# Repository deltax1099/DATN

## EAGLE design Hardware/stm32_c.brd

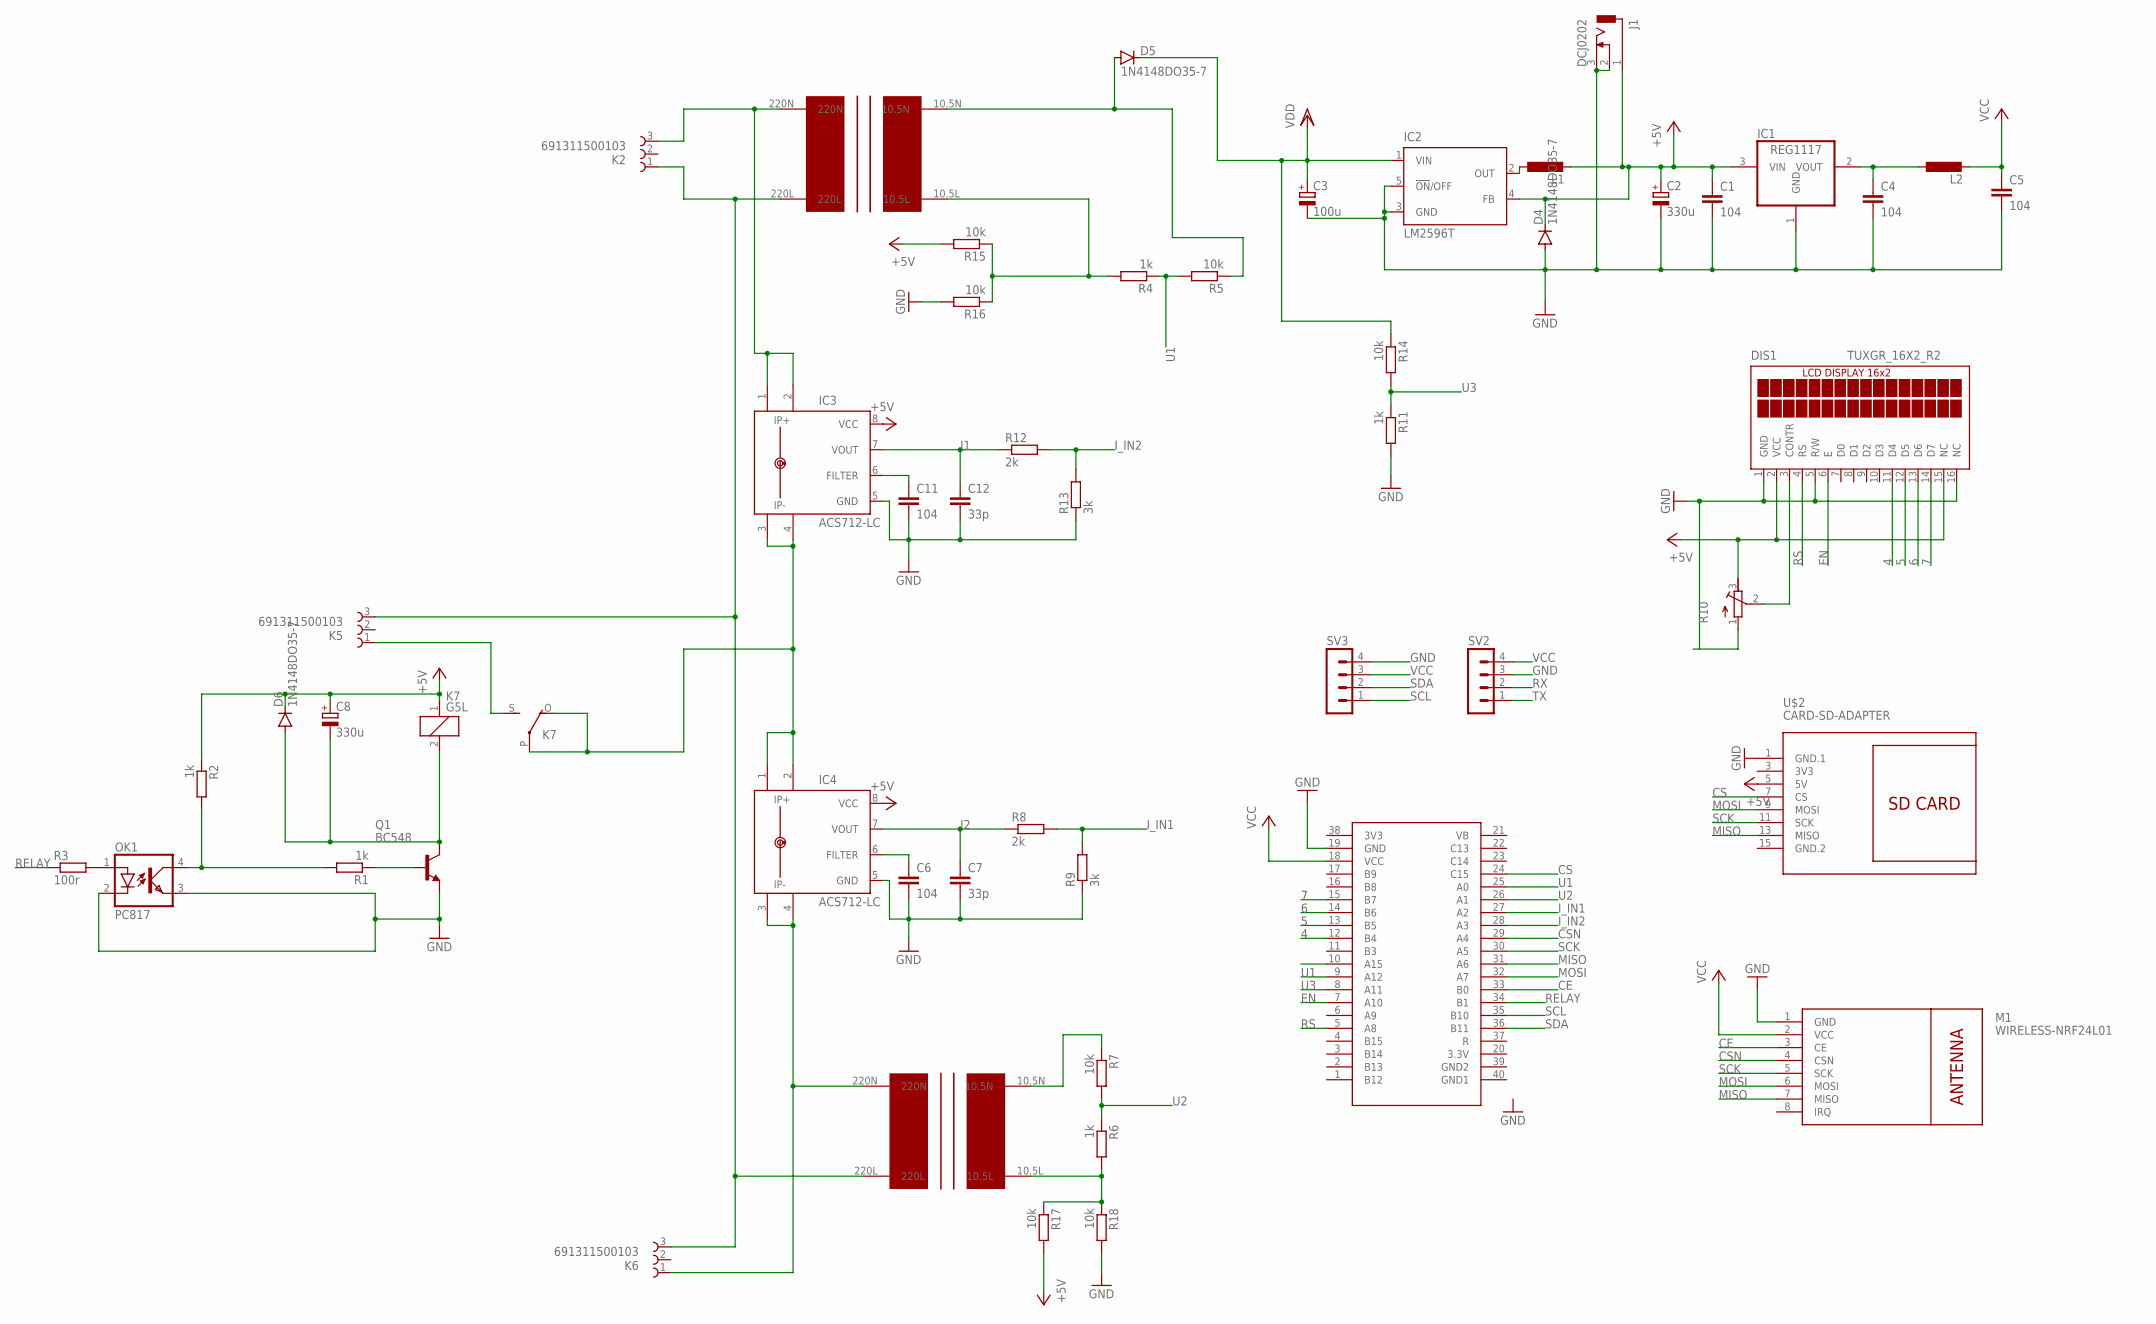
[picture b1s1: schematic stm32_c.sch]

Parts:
C1, C4, C5, C6, C11: 104; C050-025X075
C2, C8: 330u; E2,5-7
C3: 100u; E2,5-7
C7, C12: 33p; C050-025X075
D4, D5, D6: 1N4148DO35-7; DO35-7
DIS1: TUXGR_16X2_R2
IC1: REG1117; SOT223
IC2: LM2596T; T05D
IC3, IC4: ACS712-LC; SOIC8
J1: DCJ0202
K2, K5, K6: 691311500103
K7: G5L; G5LE
L1, L2: L-EU6000-XXX-RC; 6000-XXXX-RC
M1: WIRELESS-NRF24L01
OK1: PC817; DIL04
Q1: BC548; TO92-EBC
R1, R2, R4, R6, R11: 1k; 0207/7
R3: 100r; 0207/7
R5, R7, R14, R15, R16, R17, R18: 10k; 0207/7
R8, R12: 2k; 0207/7
R9, R13: 3k; 0207/7
R10: R-TRIMM3339P; RTRIM3339P
SV2, SV3: MA04-1
U$1: KIT_STM32F103
U$2: CARD-SD-ADAPTER
U$3, U$4: BIENAP(10.5)_BIEN_AP

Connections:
3V3: U$2.3 (3V3)
4: DIS1.11 (D4), U$1.12 (B4)
5: DIS1.12 (D5), U$1.13 (B5)
6: DIS1.13 (D6), U$1.14 (B6)
7: DIS1.14 (D7), U$1.15 (B7)
+5V: C1.1, C2.+, C8.+, D4.C, D6.C, DIS1.2 (VCC), DIS1.15 (NC), IC1.3 (VIN), IC2.4 (FB), IC3.8 (VCC), IC4.8 (VCC), J1.1, K7.1, L1.2, R2.1, R10.3 (E), R15.2, R17.2, U$2.5 (5V)
CE: M1.3 (CE), U$1.33 (B0)
CS: U$1.24 (C15), U$2.7 (CS)
CSN: M1.4 (CSN), U$1.29 (A4)
EN: DIS1.6 (E), U$1.7 (A10)
GND: C1.2, C2.-, C3.-, C4.2, C5.2, C6.2, C7.2, C11.2, C12.2, D4.A, DIS1.1 (GND), DIS1.5 (R/W), DIS1.16 (NC), IC1.1 (GND), IC2.3 (GND), IC2.5 (!ON!/OFF), IC3.5 (GND), IC4.5 (GND), J1.2, J1.3, M1.1 (GND), OK1.2 (C), OK1.3 (EMIT), Q1.E, R9.1, R10.1 (A), R11.2, R13.1, R16.2, R18.2, SV2.3, SV3.4, U$1.19 (GND), U$2.1 (GND.1)
GND.2: U$2.15 (GND.2)
I1: C12.1, IC3.7 (VOUT), R12.1
I2: C7.1, IC4.7 (VOUT), R8.1
I_IN1: R8.2, R9.2, U$1.27 (A2)
I_IN2: R12.2, R13.2, U$1.28 (A3)
MISO: M1.7 (MISO), U$1.31 (A6), U$2.13 (MISO)
MOSI: M1.6 (MOSI), U$1.32 (A7), U$2.9 (MOSI)
unnamed: DIS1.3 (CONTR), R10.2 (S)
unnamed: C4.1, IC1.2 (VOUT), L2.1
unnamed: IC3.1 (IP+), IC3.2 (IP+1), K2.3, U$3.220N
unnamed: R4.2, R15.1, R16.1, U$3.10.5L
unnamed: D5.A, R5.1, U$3.10.5N
unnamed: IC3.3 (IP-), IC3.4 (IP-1), IC4.1 (IP+), IC4.2 (IP+1), K7.O, K7.P
unnamed: C6.1, IC4.6 (FILTER)
unnamed: IC2.2 (OUT), L1.1
unnamed: R6.2, R17.1, R18.1, U$4.10.5L
unnamed: K5.1, K7.S
unnamed: Q1.B, R1.1
unnamed: C8.-, D6.A, K7.2, Q1.C
unnamed: OK1.4 (COL), R1.2, R2.2
unnamed: IC4.3 (IP-), IC4.4 (IP-1), K6.1, U$4.220N
unnamed: OK1.1 (A), R3.2
unnamed: K2.1, K5.3, K6.3, U$3.220L, U$4.220L
unnamed: R7.1, U$4.10.5N
unnamed: C11.1, IC3.6 (FILTER)
RELAY: R3.1, U$1.34 (B1)
RS: DIS1.4 (RS), U$1.5 (A8)
RX: SV2.2
SCK: M1.5 (SCK), U$1.30 (A5), U$2.11 (SCK)
SCL: SV3.1, U$1.35 (B10)
SDA: SV3.2, U$1.36 (B11)
TX: SV2.1
U1: R4.1, R5.2, U$1.9 (A12), U$1.25 (A0)
U2: R6.1, R7.2, U$1.26 (A1)
U3: R11.1, R14.2, U$1.8 (A11)
VCC: C5.1, L2.2, M1.2 (VCC), SV2.4, SV3.3, U$1.18 (VCC)
VDD: C3.+, D5.C, IC2.1 (VIN), R14.1

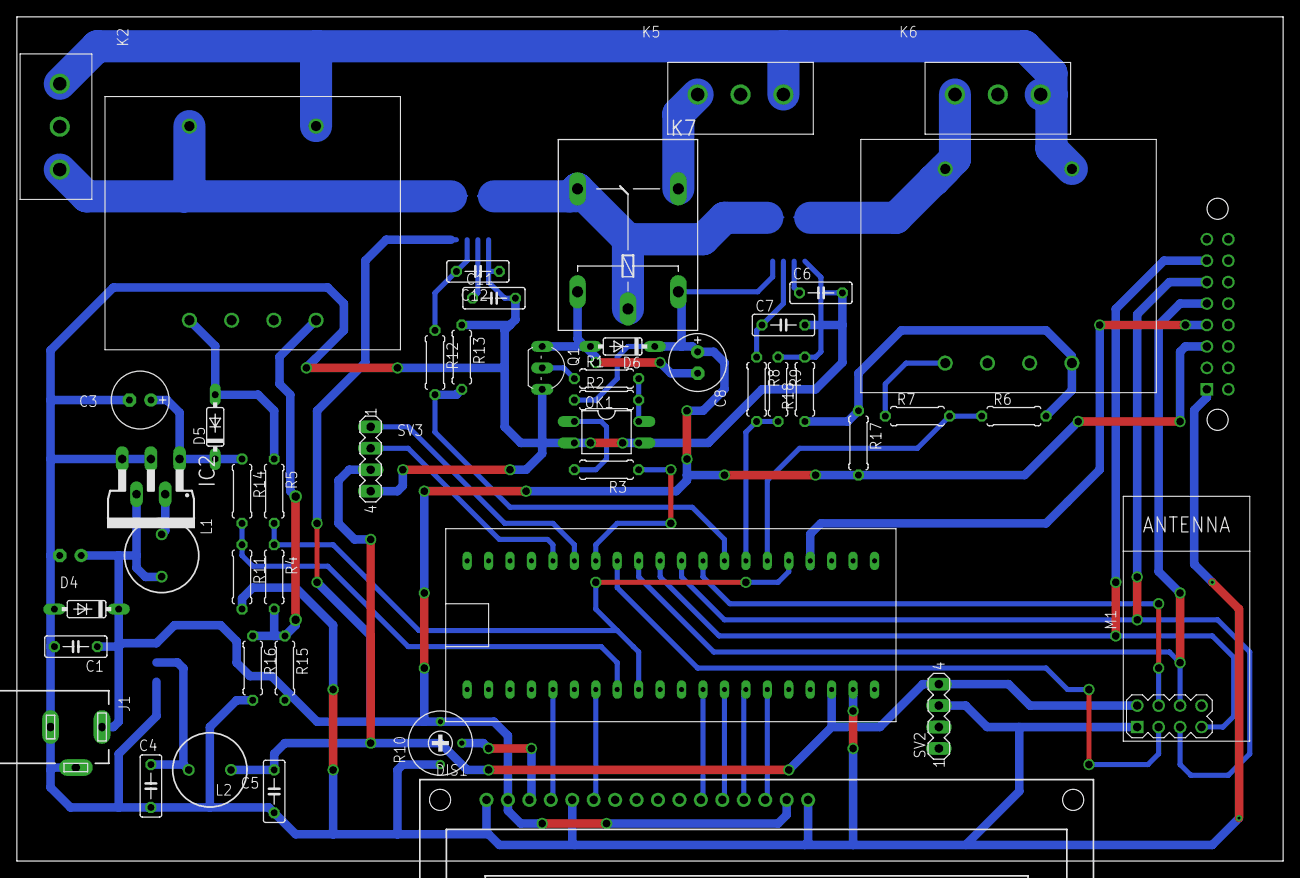
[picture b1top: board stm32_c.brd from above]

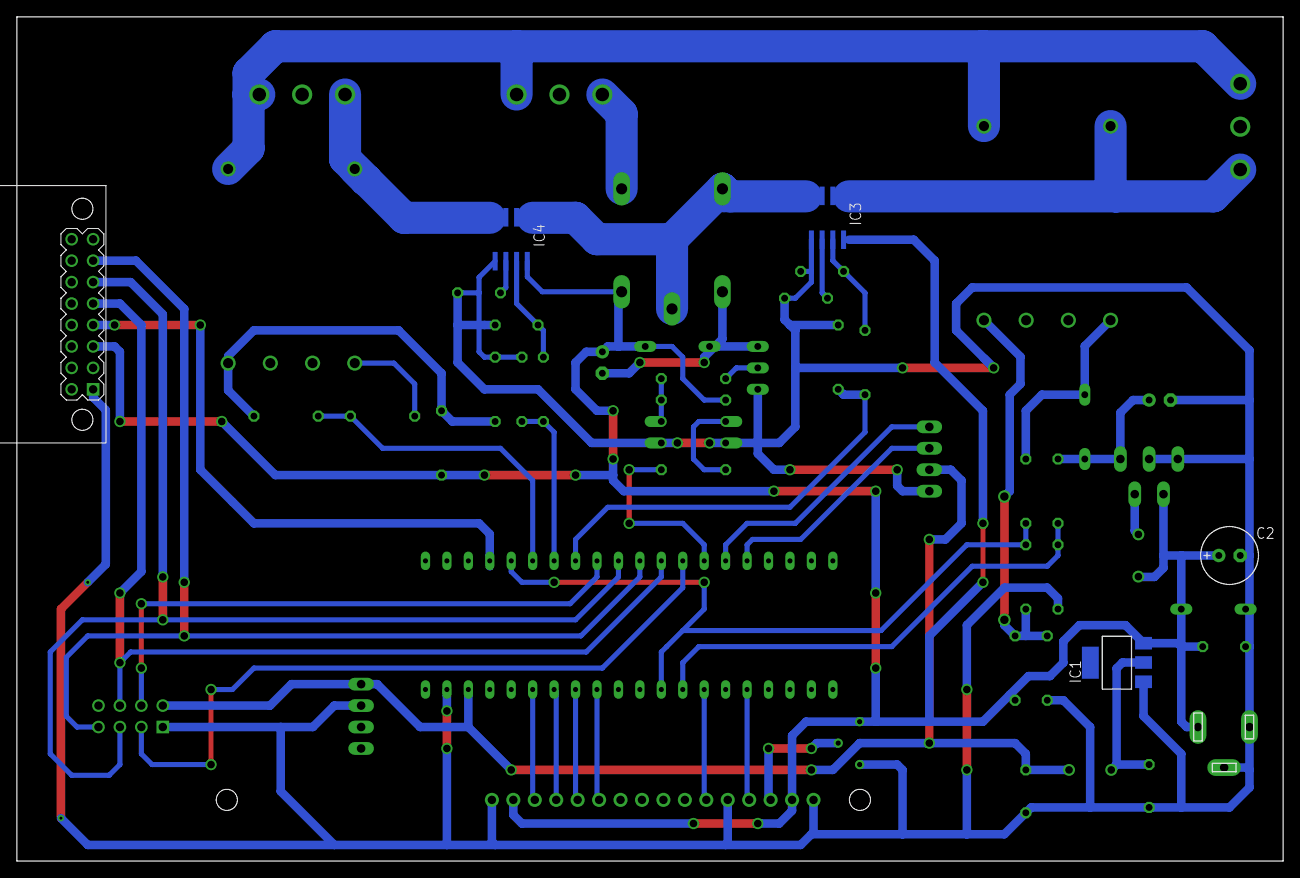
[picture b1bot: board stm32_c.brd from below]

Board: 2 copper layers, 150.0 x 100.0 mm, 52 parts (5 on the bottom side), 44 nets.

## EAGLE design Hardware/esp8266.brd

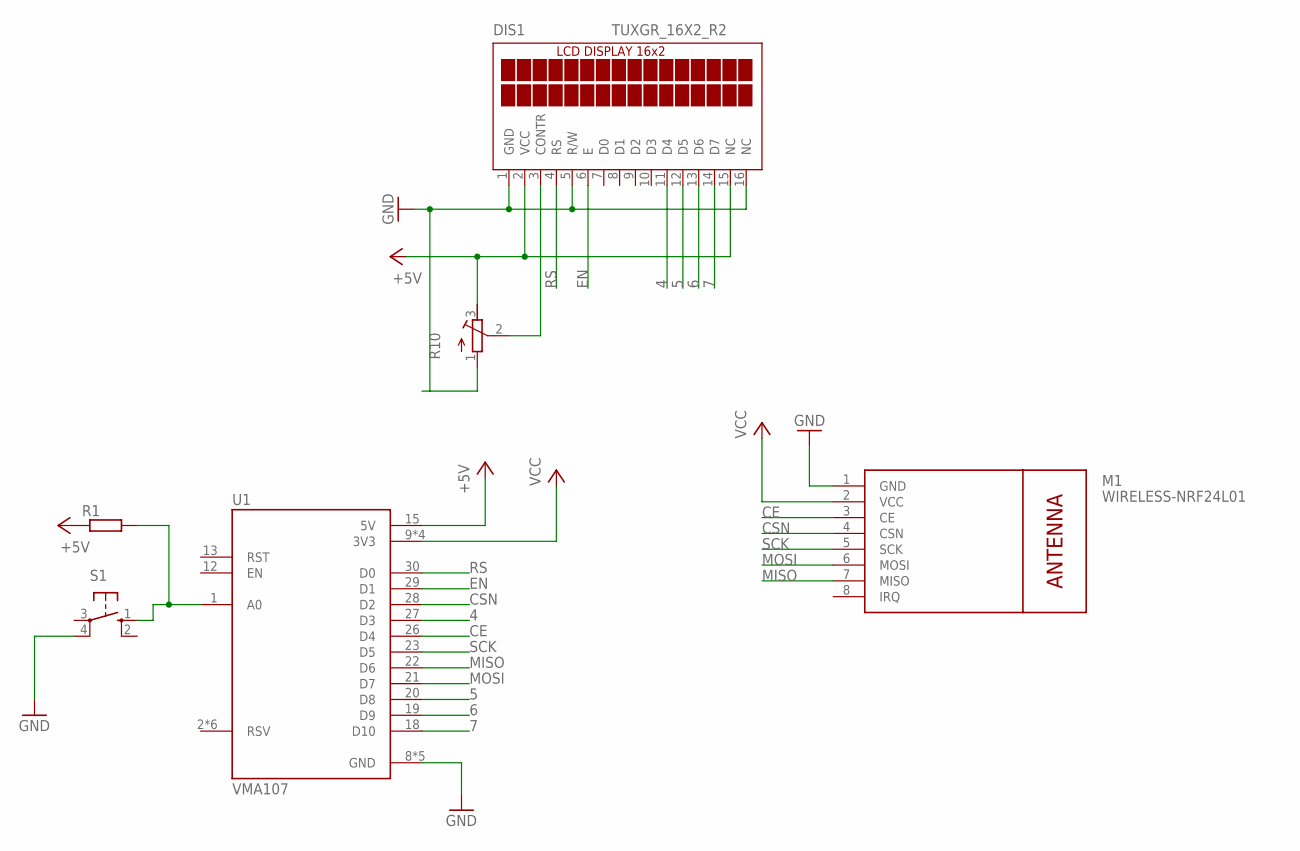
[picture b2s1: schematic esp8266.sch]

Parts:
DIS1: TUXGR_16X2_R2
M1: WIRELESS-NRF24L01
R1: R-EU_0207/7; 0207/7
R10: R-TRIMM3339P; RTRIM3339P
S1: 10-XX; B3F-10XX
U1: VMA107; MODULE_VMA107

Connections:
4: DIS1.11 (D4), U1.27 (D3)
5: DIS1.12 (D5), U1.20 (D8)
6: DIS1.13 (D6), U1.19 (D9)
7: DIS1.14 (D7), U1.18 (D10)
+5V: DIS1.2 (VCC), DIS1.15 (NC), R1.1, R10.3 (E), U1.15 (5V)
CE: M1.3 (CE), U1.26 (D4)
CSN: M1.4 (CSN), U1.28 (D2)
EN: DIS1.6 (E), U1.29 (D1)
GND: DIS1.1 (GND), DIS1.5 (R/W), DIS1.16 (NC), M1.1 (GND), R10.1 (A), S1.4 (P1), U1.8 (GND), U1.10 (GND), U1.14 (GND), U1.17 (GND), U1.24 (GND)
MISO: M1.7 (MISO), U1.22 (D6)
MOSI: M1.6 (MOSI), U1.21 (D7)
unnamed: DIS1.3 (CONTR), R10.2 (S)
unnamed: R1.2, S1.1 (S), U1.1 (A0)
RS: DIS1.4 (RS), U1.30 (D0)
SCK: M1.5 (SCK), U1.23 (D5)
VCC: M1.2 (VCC), U1.9 (3V3), U1.11 (3V3), U1.16 (3V3), U1.25 (3V3)

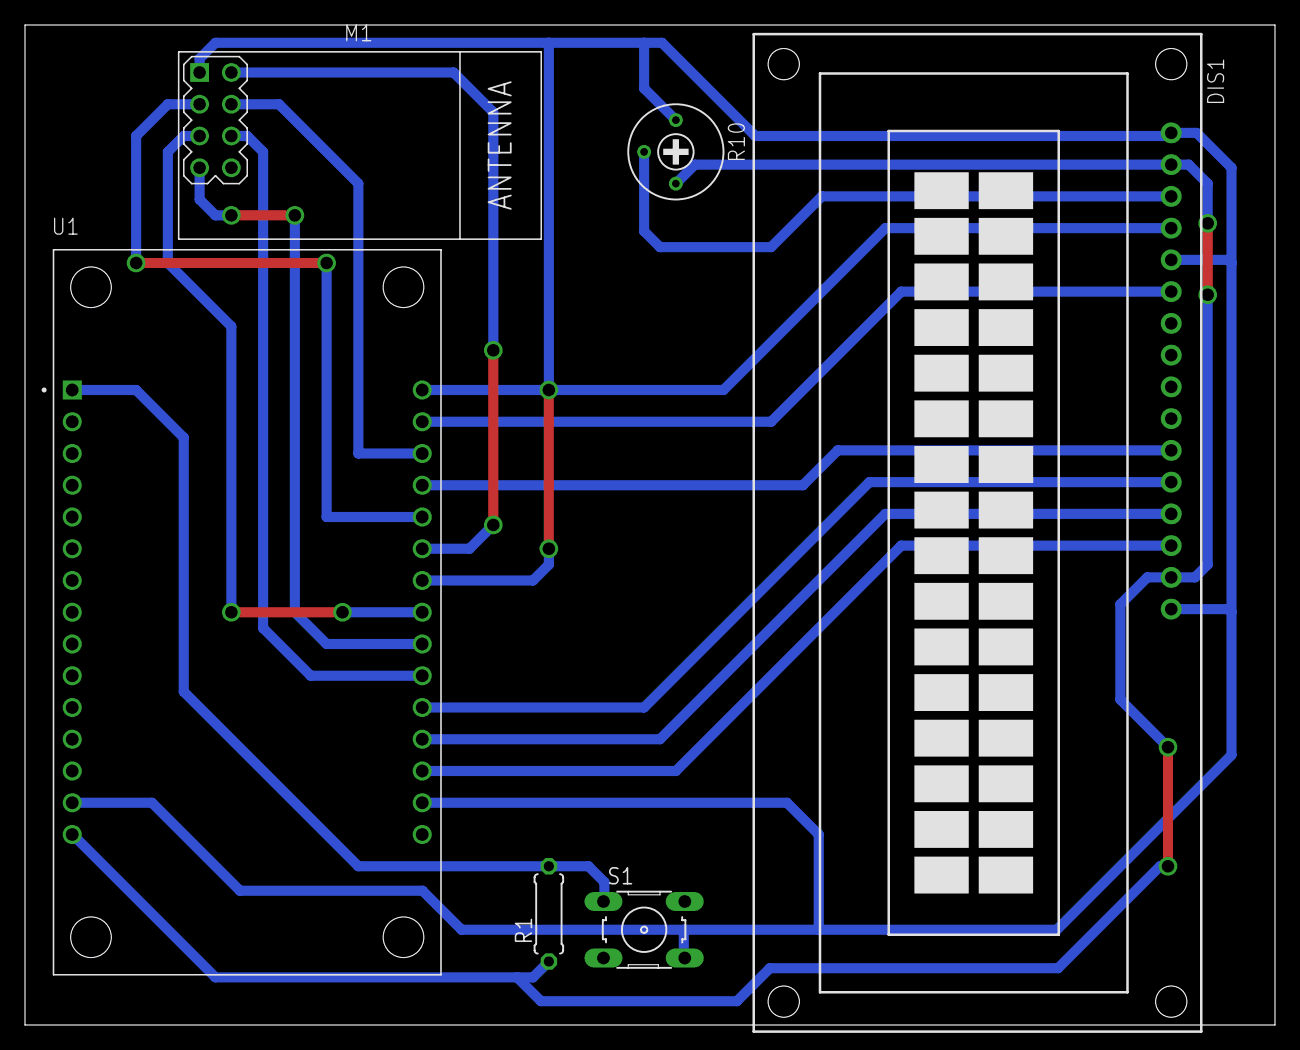
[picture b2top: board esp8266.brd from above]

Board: 2 copper layers, 100.0 x 80.0 mm, 6 parts (0 on the bottom side), 16 nets.

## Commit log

2022-08-05 Hello world
2022-08-05 Add sch and pcb
2022-08-05 modify doc and add image
2022-08-06 add image
2022-08-06 add Ket luan
2022-08-06 add overview
2022-08-06 add Thong so thiet bi
2022-08-06 modify docx
2022-08-11 go hard go hard
2022-08-12 bo sung

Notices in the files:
parts and their libraries:
diy-modules: Released under the Creative Commons Attribution 4.0 International License: http://creativecommons.org/licenses/by/4.0
Wurth_Elektronik_Electromechanic_Termina: Copyright: Würth Elektronik
